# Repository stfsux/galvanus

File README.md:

Galvanus
--------

Galvanus is a 4-GPIO board with isolated grounds. It's based on the MAX12931
which provides a galvanic isolation. Single buffers are used in order to switch
between Input/Output mode.

PCB
---

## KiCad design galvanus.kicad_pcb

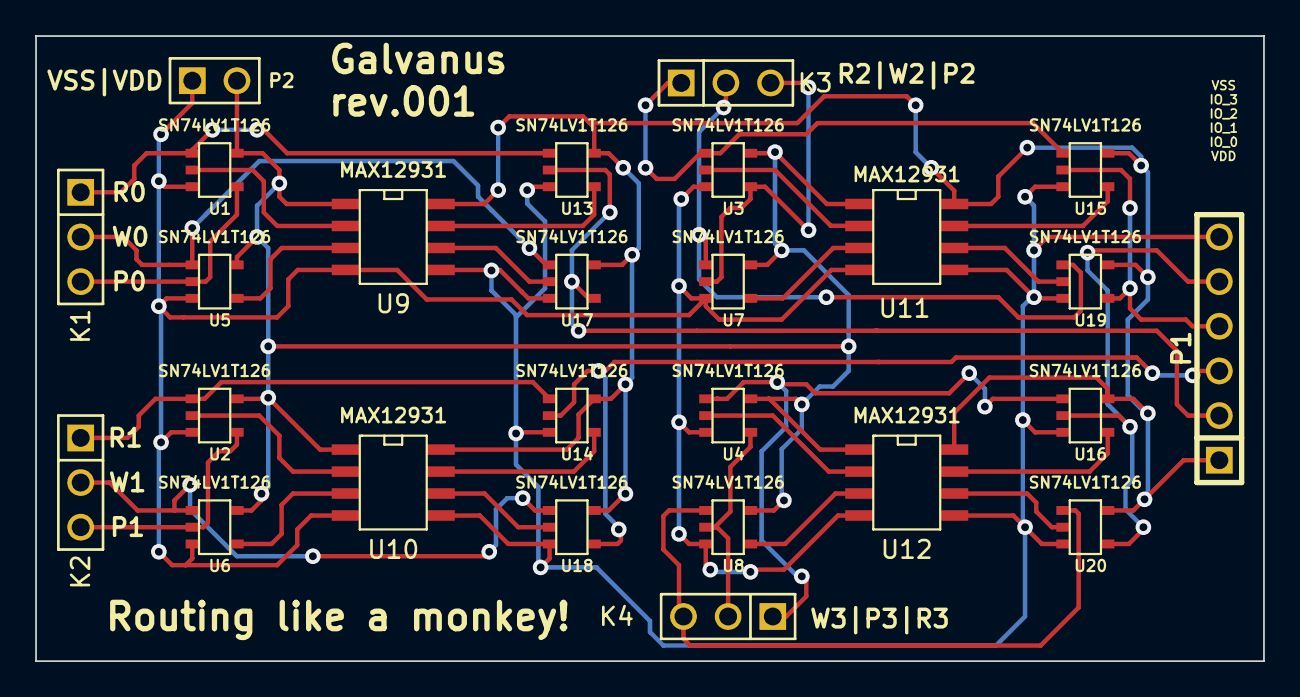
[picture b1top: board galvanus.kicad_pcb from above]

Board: 2 copper layers, 69.9 x 35.6 mm, 26 parts (0 on the bottom side), 36 nets.

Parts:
K1, K2, K3, K4: CONN_3; PIN_ARRAY_3X1
P1: CONN_6; PIN_ARRAY-6X1
P2: CONN_2; PIN_ARRAY_2X1
U1, U2, U3, U4, U5, U6, U7, U8, U13, U14, U15, U16, U17, U18, U19, U20: SN74LV1T126; SOT23-5
U9, U10, U11, U12: MAX12931; SOIC-8_N

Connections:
IO_0: P1.2, U13.2, U17.4
IO_1: P1.3, U14.2, U18.4
IO_2: P1.4, U15.2, U19.4
IO_3: P1.5, U16.2, U20.4
MCU_P0: K1.3, U1.4, U5.2
MCU_P1: K2.3, U2.4, U6.2
MCU_P2: K3.3, U3.4, U7.2
MCU_P3: K4.2, U4.4, U8.2
MCU_R0: K1.1, U1.1, U13.1
MCU_R1: K2.1, U2.1, U14.1
MCU_R2: K3.1, U3.1, U15.1
MCU_R3: K4.1, U4.1, U16.1
MCU_VDD: P2.2, U1.5, U2.5, U3.5, U4.5, U5.5, U6.5, U7.5, U8.5, U9.1, U10.1, U11.1, U12.1
MCU_VSS: P2.1, U1.3, U2.3, U3.3, U4.3, U5.3, U6.3, U7.3, U8.3, U9.4, U10.4, U11.4, U12.4
MCU_W0: K1.2, U5.1, U17.1
MCU_W1: K2.2, U6.1, U18.1
MCU_W2: K3.2, U7.1, U19.1
MCU_W3: K4.3, U8.1, U20.1
unnamed: U12.6, U20.2
unnamed: U12.7, U16.4
unnamed: U4.2, U12.2
unnamed: U8.4, U12.3
unnamed: U11.6, U19.2
unnamed: U11.7, U15.4
unnamed: U3.2, U11.2
unnamed: U7.4, U11.3
unnamed: U10.6, U18.2
unnamed: U5.4, U9.3
unnamed: U9.7, U13.4
unnamed: U1.2, U9.2
unnamed: U9.6, U17.2
unnamed: U6.4, U10.3
unnamed: U10.7, U14.4
unnamed: U2.2, U10.2
TARGET_VDD: P1.1, U9.8, U10.8, U11.8, U12.8, U13.5, U14.5, U15.5, U16.5, U17.5, U18.5, U19.5, U20.5
TARGET_VSS: P1.6, U9.5, U10.5, U11.5, U12.5, U13.3, U14.3, U15.3, U16.3, U17.3, U18.3, U19.3, U20.3

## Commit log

2016-10-11 Initial anal pain
2016-10-11 PDF added
2016-10-11 PCB image added
2016-10-11 README modified
2016-10-13 Panelized PCB has been added
